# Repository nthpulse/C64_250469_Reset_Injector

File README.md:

# C64_250469_Reset_Injector
Interposer for the C64 250469 "short" motherboard that allows a reset pulse to be injected at U23

See https://nthpulse.net/projects/mrom64_selector_panel/

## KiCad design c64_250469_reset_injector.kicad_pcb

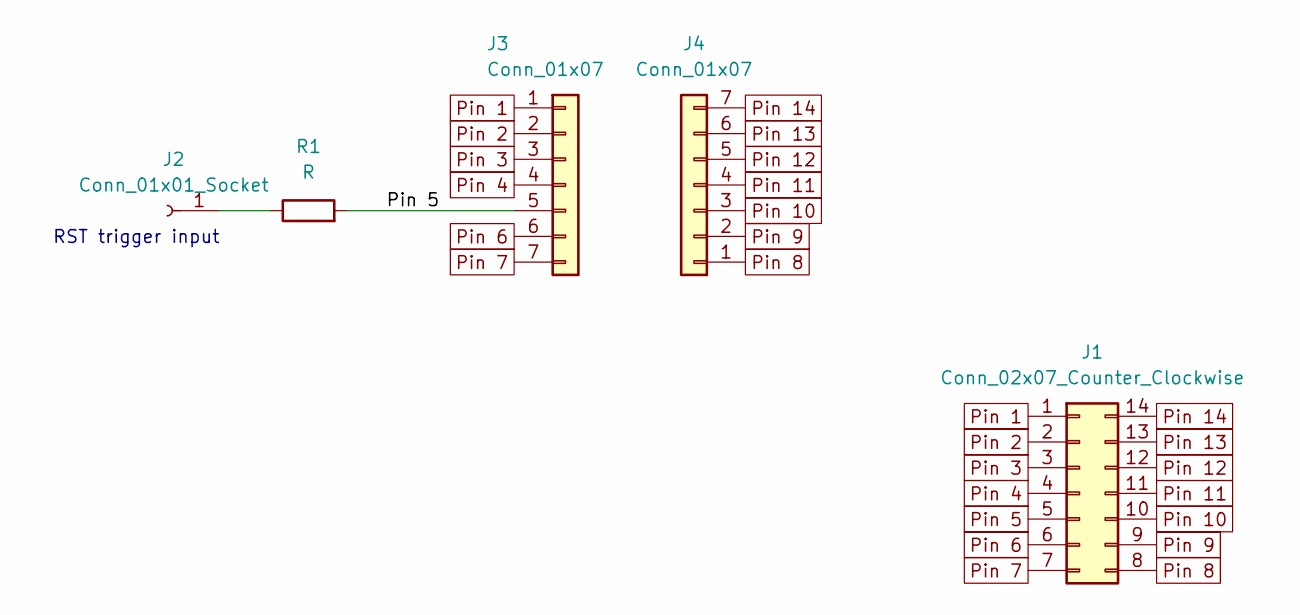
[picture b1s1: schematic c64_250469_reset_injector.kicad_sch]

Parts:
J1: Conn_02x07_Counter_Clockwise; DIP-14_W7.62mm_Socket
J2: Conn_01x01_Socket; PinHeader_1x01_P2.54mm_Vertical
J3, J4: Conn_01x07; PinHeader_1x07_P2.54mm_Vertical
R1: R; R_0805_2012Metric_Pad1.20x1.40mm_HandSolder

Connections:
unnamed: J2.1 (Pin_1_1), R1.1
Pin 1: J1.1, J3.1
Pin 2: J1.2, J3.2
Pin 3: J1.3, J3.3
Pin 4: J1.4, J3.4
Pin 5: J1.5, J3.5, R1.2
Pin 6: J1.6, J3.6
Pin 7: J1.7, J3.7
Pin 8: J1.8, J4.1
Pin 9: J1.9, J4.2
Pin 10: J1.10, J4.3
Pin 11: J1.11, J4.4
Pin 12: J1.12, J4.5
Pin 13: J1.13, J4.6
Pin 14: J1.14, J4.7

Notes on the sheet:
RST trigger input

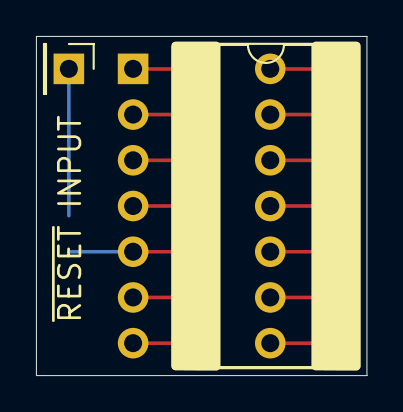
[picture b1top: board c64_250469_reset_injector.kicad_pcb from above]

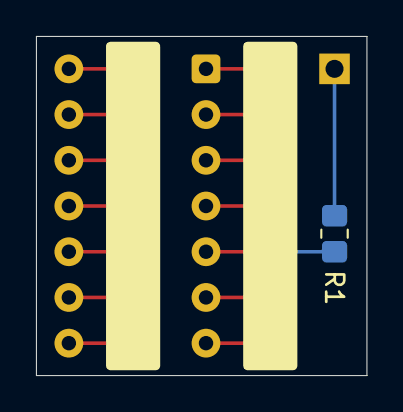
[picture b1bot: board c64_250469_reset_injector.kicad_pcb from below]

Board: 2 copper layers, 18.4 x 18.8 mm, 5 parts (3 on the bottom side), 15 nets.
